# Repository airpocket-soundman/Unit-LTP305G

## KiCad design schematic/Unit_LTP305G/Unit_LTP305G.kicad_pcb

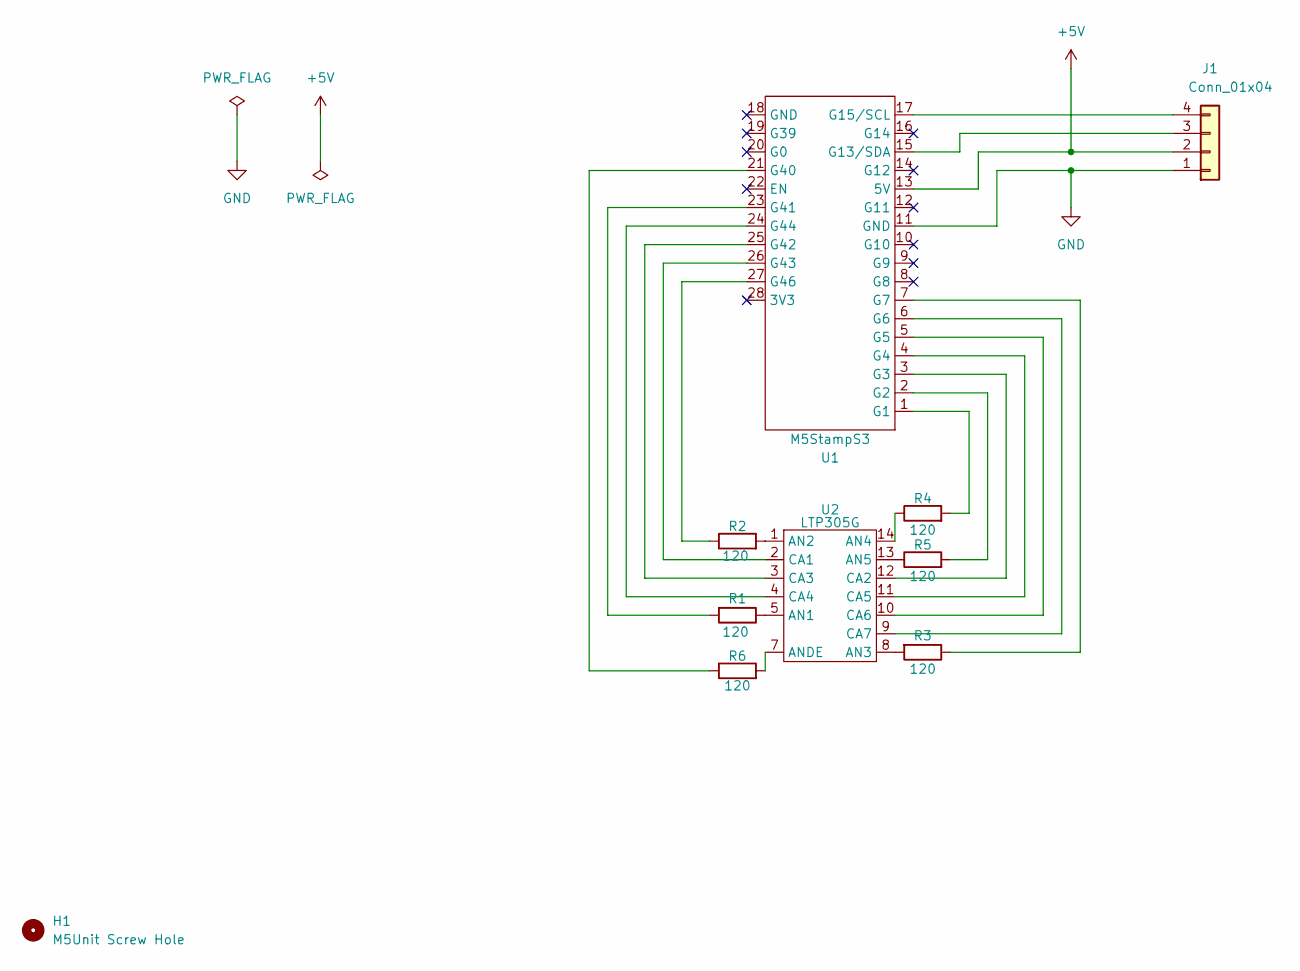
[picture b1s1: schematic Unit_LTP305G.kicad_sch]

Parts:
H1: M5Unit Screw Hole; unit_mounting_hole
J1: Conn_01x04; HY2.0-4P
R1, R2, R3, R4, R5, R6: 120; R_0805_2012Metric_Pad1.20x1.40mm_HandSolder
U1: M5StampS3
U2: LTP305G

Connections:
+5V: J1.2, U1.13 (5V)
GND: J1.1, U1.11 (GND)
unnamed: J1.3, U1.15 (G13/SDA)
unnamed: J1.4, U1.17 (G15/SCL)
unnamed: R4.2, U1.1 (G1)
unnamed: R5.2, U1.2 (G2)
unnamed: U1.3 (G3), U2.12 (CA2)
unnamed: U1.4 (G4), U2.11 (CA5)
unnamed: U1.5 (G5), U2.10 (CA6)
unnamed: U1.6 (G6), U2.9 (CA7)
unnamed: R3.1, U1.7 (G7)
unnamed: R6.1, U1.21 (G40)
unnamed: R1.2, U1.23 (G41)
unnamed: U1.25 (G42), U2.3 (CA3)
unnamed: U1.26 (G43), U2.2 (CA1)
unnamed: U1.24 (G44), U2.4 (CA4)
unnamed: R2.1, U1.27 (G46)
unnamed: R1.1, U2.5 (AN1)
unnamed: R2.2, U2.1 (AN2)
unnamed: R3.2, U2.8 (AN3)
unnamed: R4.1, U2.14 (AN4)
unnamed: R5.1, U2.13 (AN5)
unnamed: R6.2, U2.7 (ANDE)

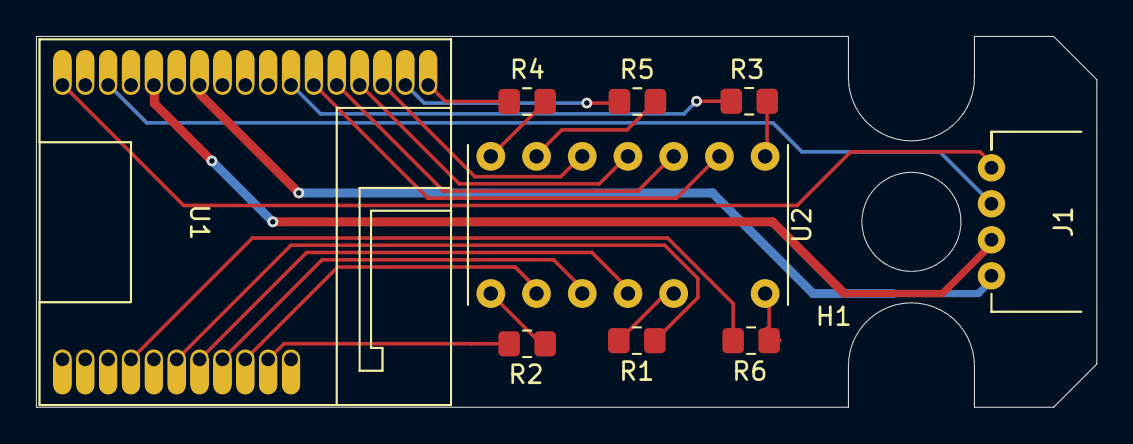
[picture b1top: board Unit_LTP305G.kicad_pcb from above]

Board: 2 copper layers, 58.9 x 20.6 mm, 10 parts (0 on the bottom side), 23 nets.

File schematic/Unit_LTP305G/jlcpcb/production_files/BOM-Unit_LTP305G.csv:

Comment,Designator,Footprint,LCSC
H1,M5Unit Screw Hole,unit_mounting_hole,,,0,0
J1,Conn_01x04,HY2.0-4P,,,0,0
R1,120,R_0805_2012Metric_Pad1.20x1.40mm_HandSolder,,,0,0
R2,120,R_0805_2012Metric_Pad1.20x1.40mm_HandSolder,,,0,0
R3,120,R_0805_2012Metric_Pad1.20x1.40mm_HandSolder,,,0,0
R4,120,R_0805_2012Metric_Pad1.20x1.40mm_HandSolder,,,0,0
R5,120,R_0805_2012Metric_Pad1.20x1.40mm_HandSolder,,,0,0
R6,120,R_0805_2012Metric_Pad1.20x1.40mm_HandSolder,,,0,0
U1,M5StampS3,M5StampS3,,,0,0
U2,LTP305G,LTP305G,,,0,0

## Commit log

2024-06-27 回路図制作開始
2024-06-28 基板設計
2024-07-10 schematic
2024-07-10 スケッチ
2024-07-18 arduinoコード作成
2024-07-22 ino更新
2024-07-22 test
2024-07-23 m5f,m5b更新
2024-07-23 いろいろ
2024-07-23 m5f,m5bを修正
2024-07-24 dev2.ino
